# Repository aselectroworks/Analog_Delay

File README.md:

Analog_Delay
============

Multiple function BBD Analog Delay assisted by Digital Domain. 

### Features
* Max. 1000 ms delay by 4 BBDs
* Stereo In/Out
* Monaural In/Stereo Out(ping-pong or fx+dryout)
* Tap tempo function assisted by digital domain 
* Delay effect remain or bypass selectable when fx function off
* LCD display

### Design Tools
* [KiCAD](http://www.kicad-pcb.org/)
* [atmel studio 6](http://www.atmel.com/tools/ATMELSTUDIO.aspx)

### Download
You can download this project in either [zip](https://github.com/aselectroworks/Analog_Delay/zipball/master) or [tar](https://github.com/aselectroworks/Analog_Delay/tarball/master) formats. 
You can also clone this project with [git](http://git-scm.com/) by runninng: 
```
$ git clone git://github.com/aselectroworks/Analog_Delay
```

### License
GPL v3

### Contact
atsushi.sasaki@aselectroworks.com

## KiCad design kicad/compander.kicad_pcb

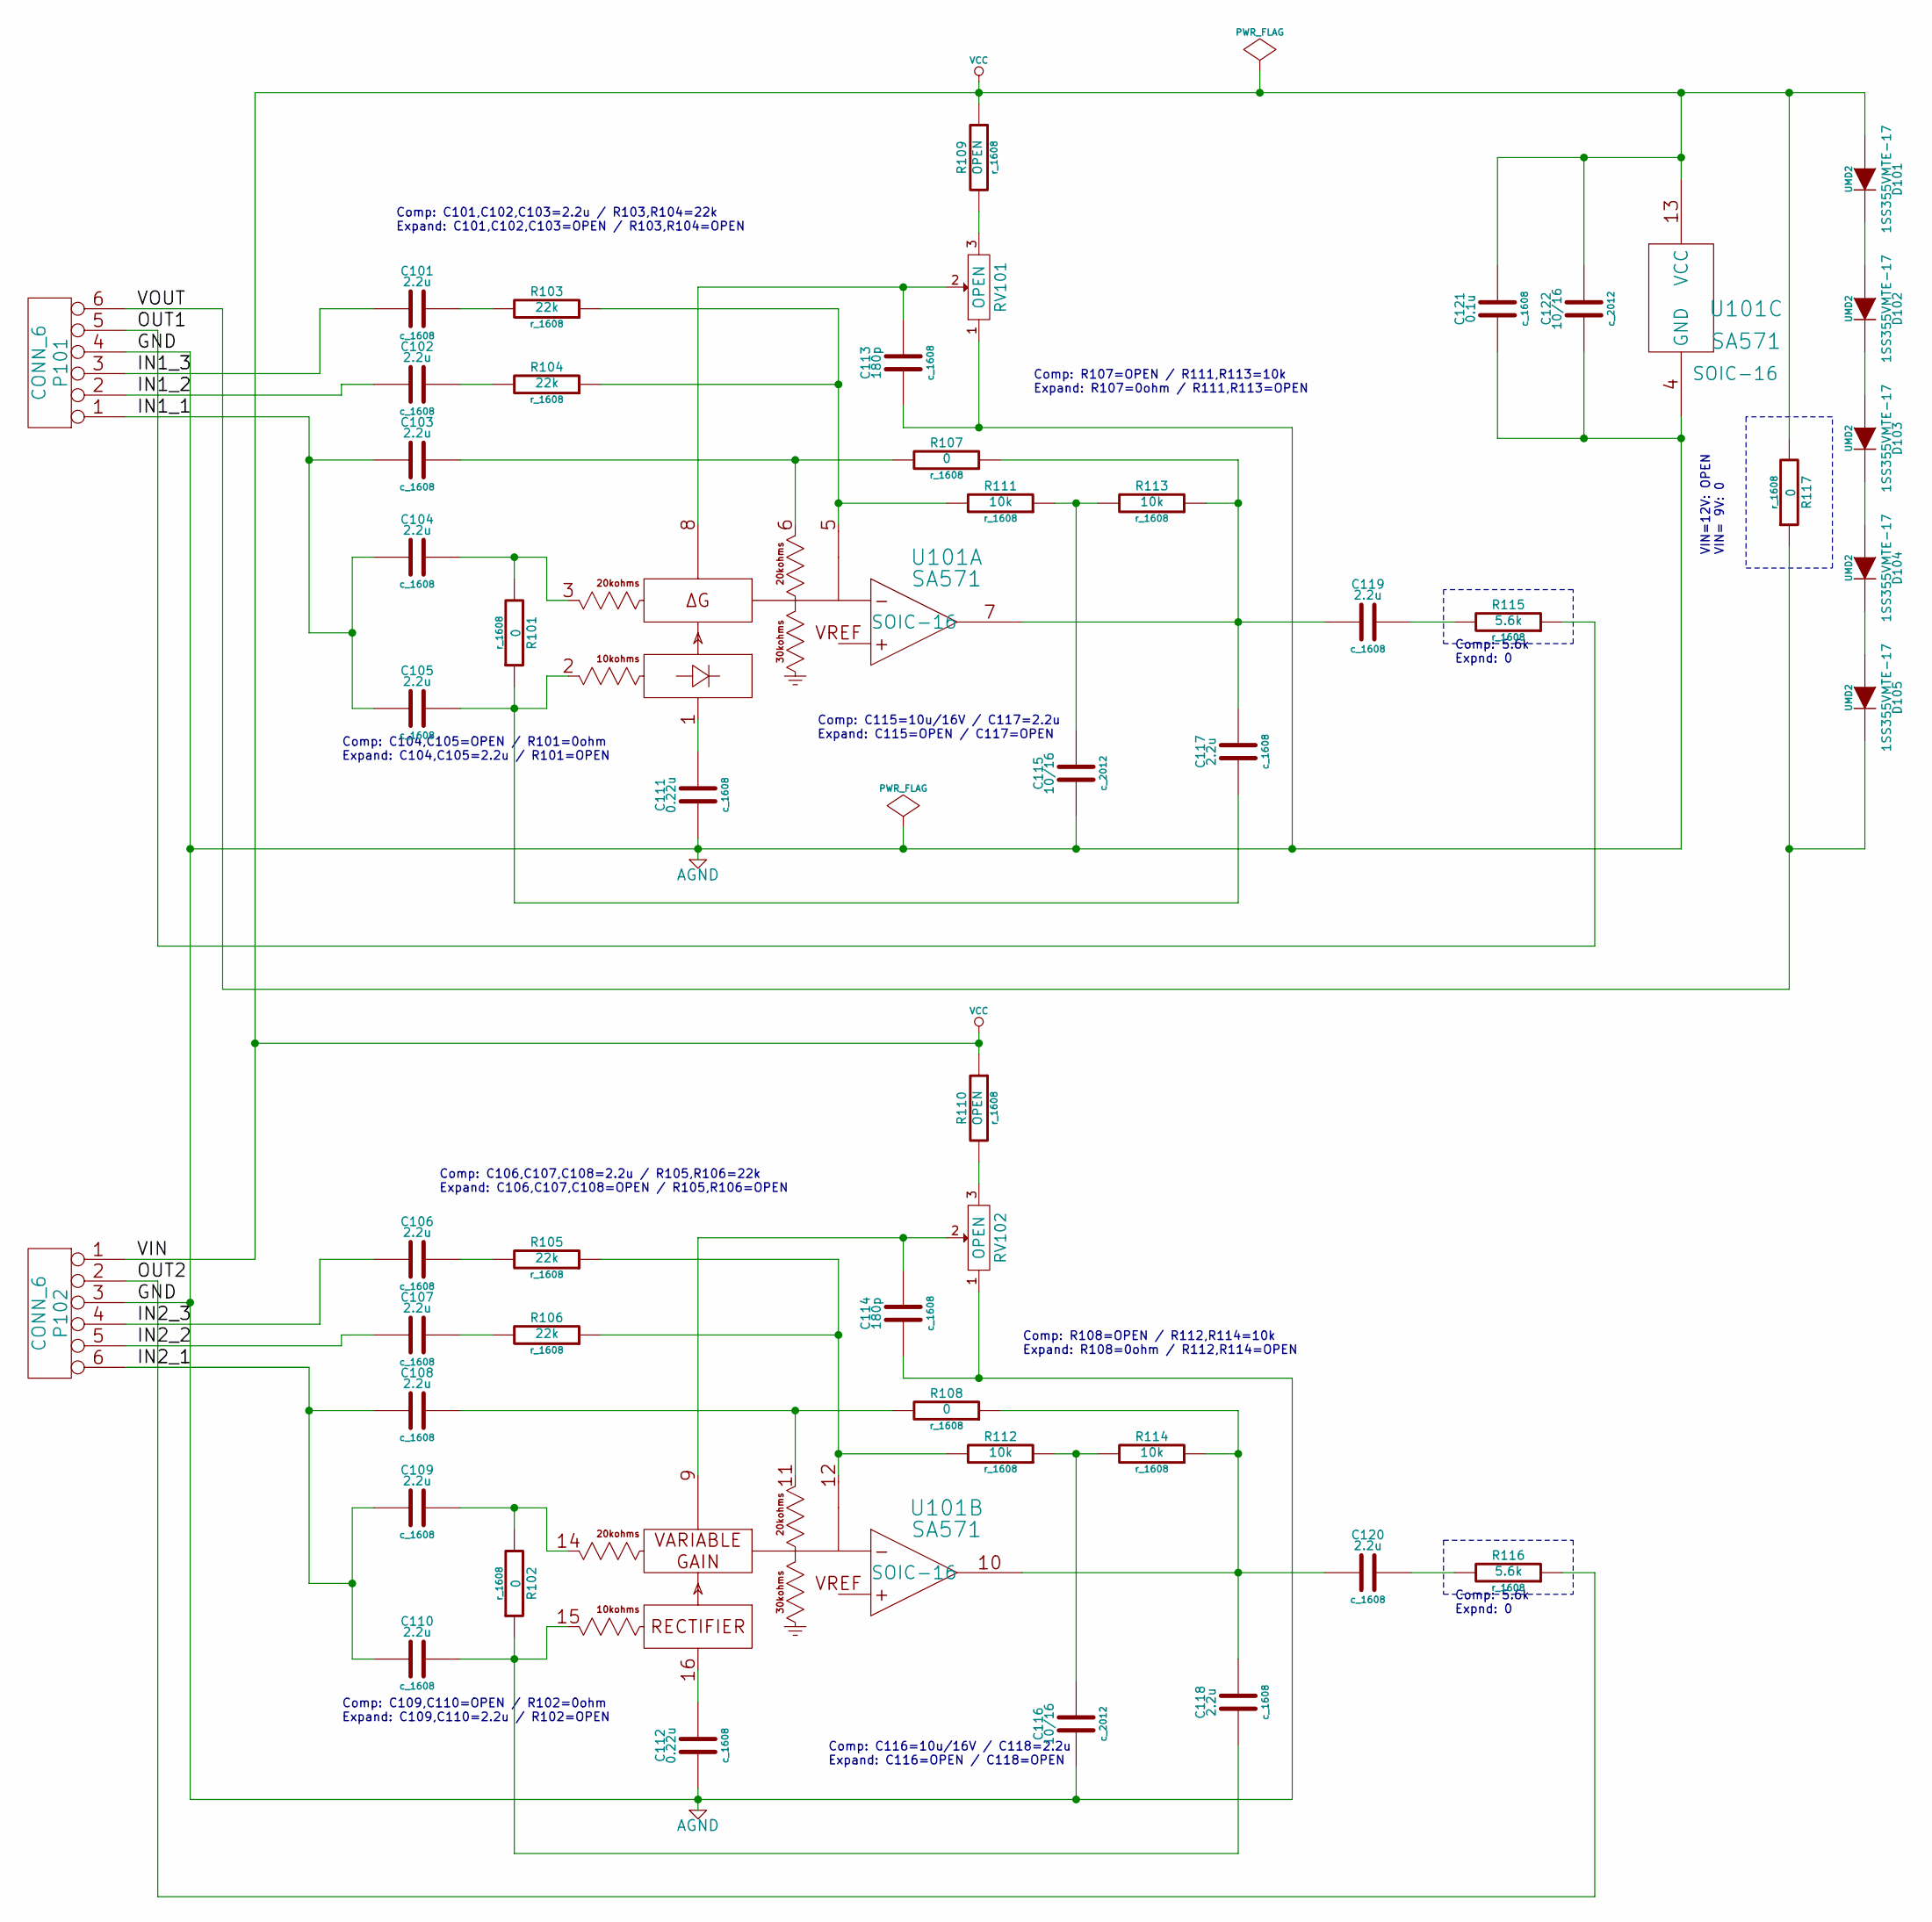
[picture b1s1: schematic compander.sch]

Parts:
C101, C102, C103, C104, C105, C106, C107, C108, C109, C110, C117, C118, C119, C120: 2.2u; c_1608
C111, C112: 0.22u; c_1608
C113, C114: 180p; c_1608
C115, C116, C122: 10/16; c_2012
C121: 0.1u; c_1608
D101, D102, D103, D104, D105: 1SS355VMTE-17; UMD2
P101, P102: CONN_6
R101, R102, R107, R108, R117: 0; r_1608
R103, R104, R105, R106: 22k; r_1608
R109, R110: OPEN; r_1608
R111, R112, R113, R114: 10k; r_1608
R115, R116: 5.6k; r_1608
RV101, RV102: OPEN
U101: SA571; SOIC-16

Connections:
/IN1_1: C103.1, C104.1, C105.1, P101.1
/IN1_2: C102.1, P101.2
/IN1_3: C101.1, P101.3
/IN2_1: C108.1, C109.1, C110.1, P102.6
/IN2_2: C107.1, P102.5
/IN2_3: C106.1, P102.4
/OUT1: P101.5, R115.1
/OUT2: P102.2, R116.1
/VOUT: D105.2 (K), P101.6, R117.1
AGND: C111.1, C112.1, C113.1, C114.1, C115.1, C116.1, C121.1, C122.1, P101.4, P102.3, RV101.1, RV102.1, U101.4 (GND)
unnamed: C114.2, RV102.2, U101.9 (THD_TRIM_2)
unnamed: R110.2, RV102.3
unnamed: C104.2, R101.2, U101.3 (DG_CELL_IN_1)
unnamed: R105.1, R106.1, R112.2, U101.12 (INV._IN_2)
unnamed: C107.2, R106.2
unnamed: C106.2, R105.2
unnamed: C120.2, R116.2
unnamed: C115.2, R111.1, R113.2
unnamed: R103.1, R104.1, R111.2, U101.5 (INV._IN_1)
unnamed: C102.2, R104.2
unnamed: C101.2, R103.2
unnamed: C119.2, R115.2
unnamed: C105.2, C117.1, R101.1, U101.2 (RECT_IN_1)
unnamed: C116.2, R112.1, R114.2
unnamed: C111.2, U101.1 (RECT_CAP_1)
unnamed: C103.2, R107.2, U101.6 (RES._R3_1)
unnamed: C117.2, C119.1, R107.1, R113.1, U101.7 (OUTPUT_1)
unnamed: D101.2 (K), D102.1 (A)
unnamed: D104.2 (K), D105.1 (A)
unnamed: D103.2 (K), D104.1 (A)
unnamed: D102.2 (K), D103.1 (A)
unnamed: C112.2, U101.16 (RECT_CAP_2)
unnamed: C108.2, R108.2, U101.11 (RES._R3_2)
unnamed: C118.2, C120.1, R108.1, R114.1, U101.10 (OUTPUT_2)
unnamed: C110.2, C118.1, R102.1, U101.15 (RECT_IN_2)
unnamed: C109.2, R102.2, U101.14 (DG_CELL_IN_2)
unnamed: C113.2, RV101.2, U101.8 (THD_TRIM_1)
unnamed: R109.2, RV101.3
VCC: C121.2, C122.2, D101.1 (A), P102.1, R109.1, R110.1, R117.2, U101.13 (VCC)

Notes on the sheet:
Comp: 5.6k Expnd: 0
VIN=12V: OPEN VIN= 9V: 0
Comp: C104,C105=OPEN / R101=0ohm Expand: C104,C105=2.2u / R101=OPEN
Comp: C109,C110=OPEN / R102=0ohm Expand: C109,C110=2.2u / R102=OPEN
Comp: C106,C107,C108=2.2u / R105,R106=22k Expand: C106,C107,C108=OPEN / R105,R106=OPEN
Comp: C101,C102,C103=2.2u / R103,R104=22k Expand: C101,C102,C103=OPEN / R103,R104=OPEN
Comp: R107=OPEN / R111,R113=10k Expand: R107=0ohm / R111,R113=OPEN
Comp: R108=OPEN / R112,R114=10k Expand: R108=0ohm / R112,R114=OPEN
Comp: C116=10u/16V / C118=2.2u Expand: C116=OPEN / C118=OPEN
Comp: C115=10u/16V / C117=2.2u Expand: C115=OPEN / C117=OPEN

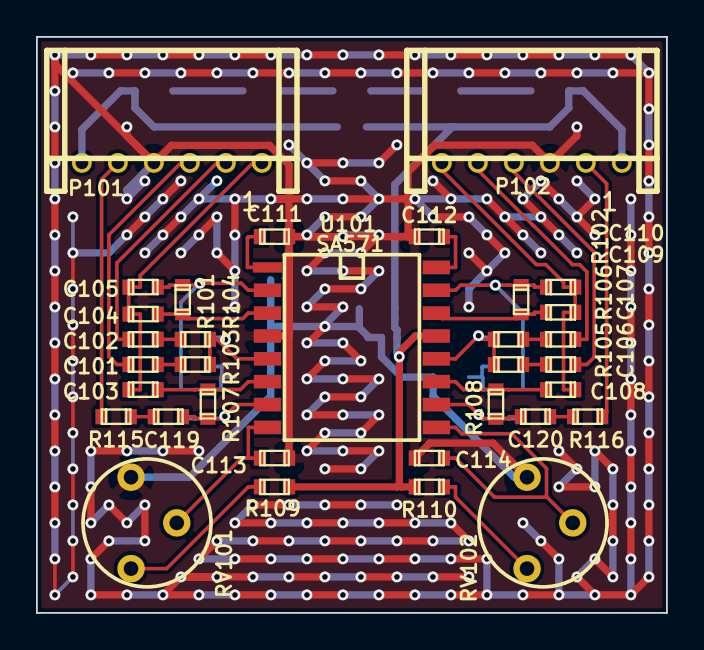
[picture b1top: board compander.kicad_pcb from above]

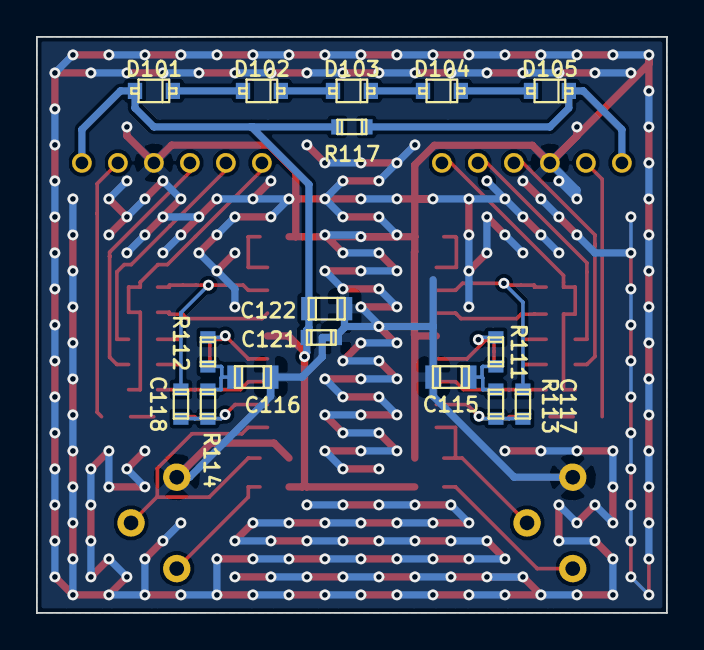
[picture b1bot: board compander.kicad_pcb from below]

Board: 2 copper layers, 35.0 x 32.0 mm, 49 parts (16 on the bottom side), 39 nets.

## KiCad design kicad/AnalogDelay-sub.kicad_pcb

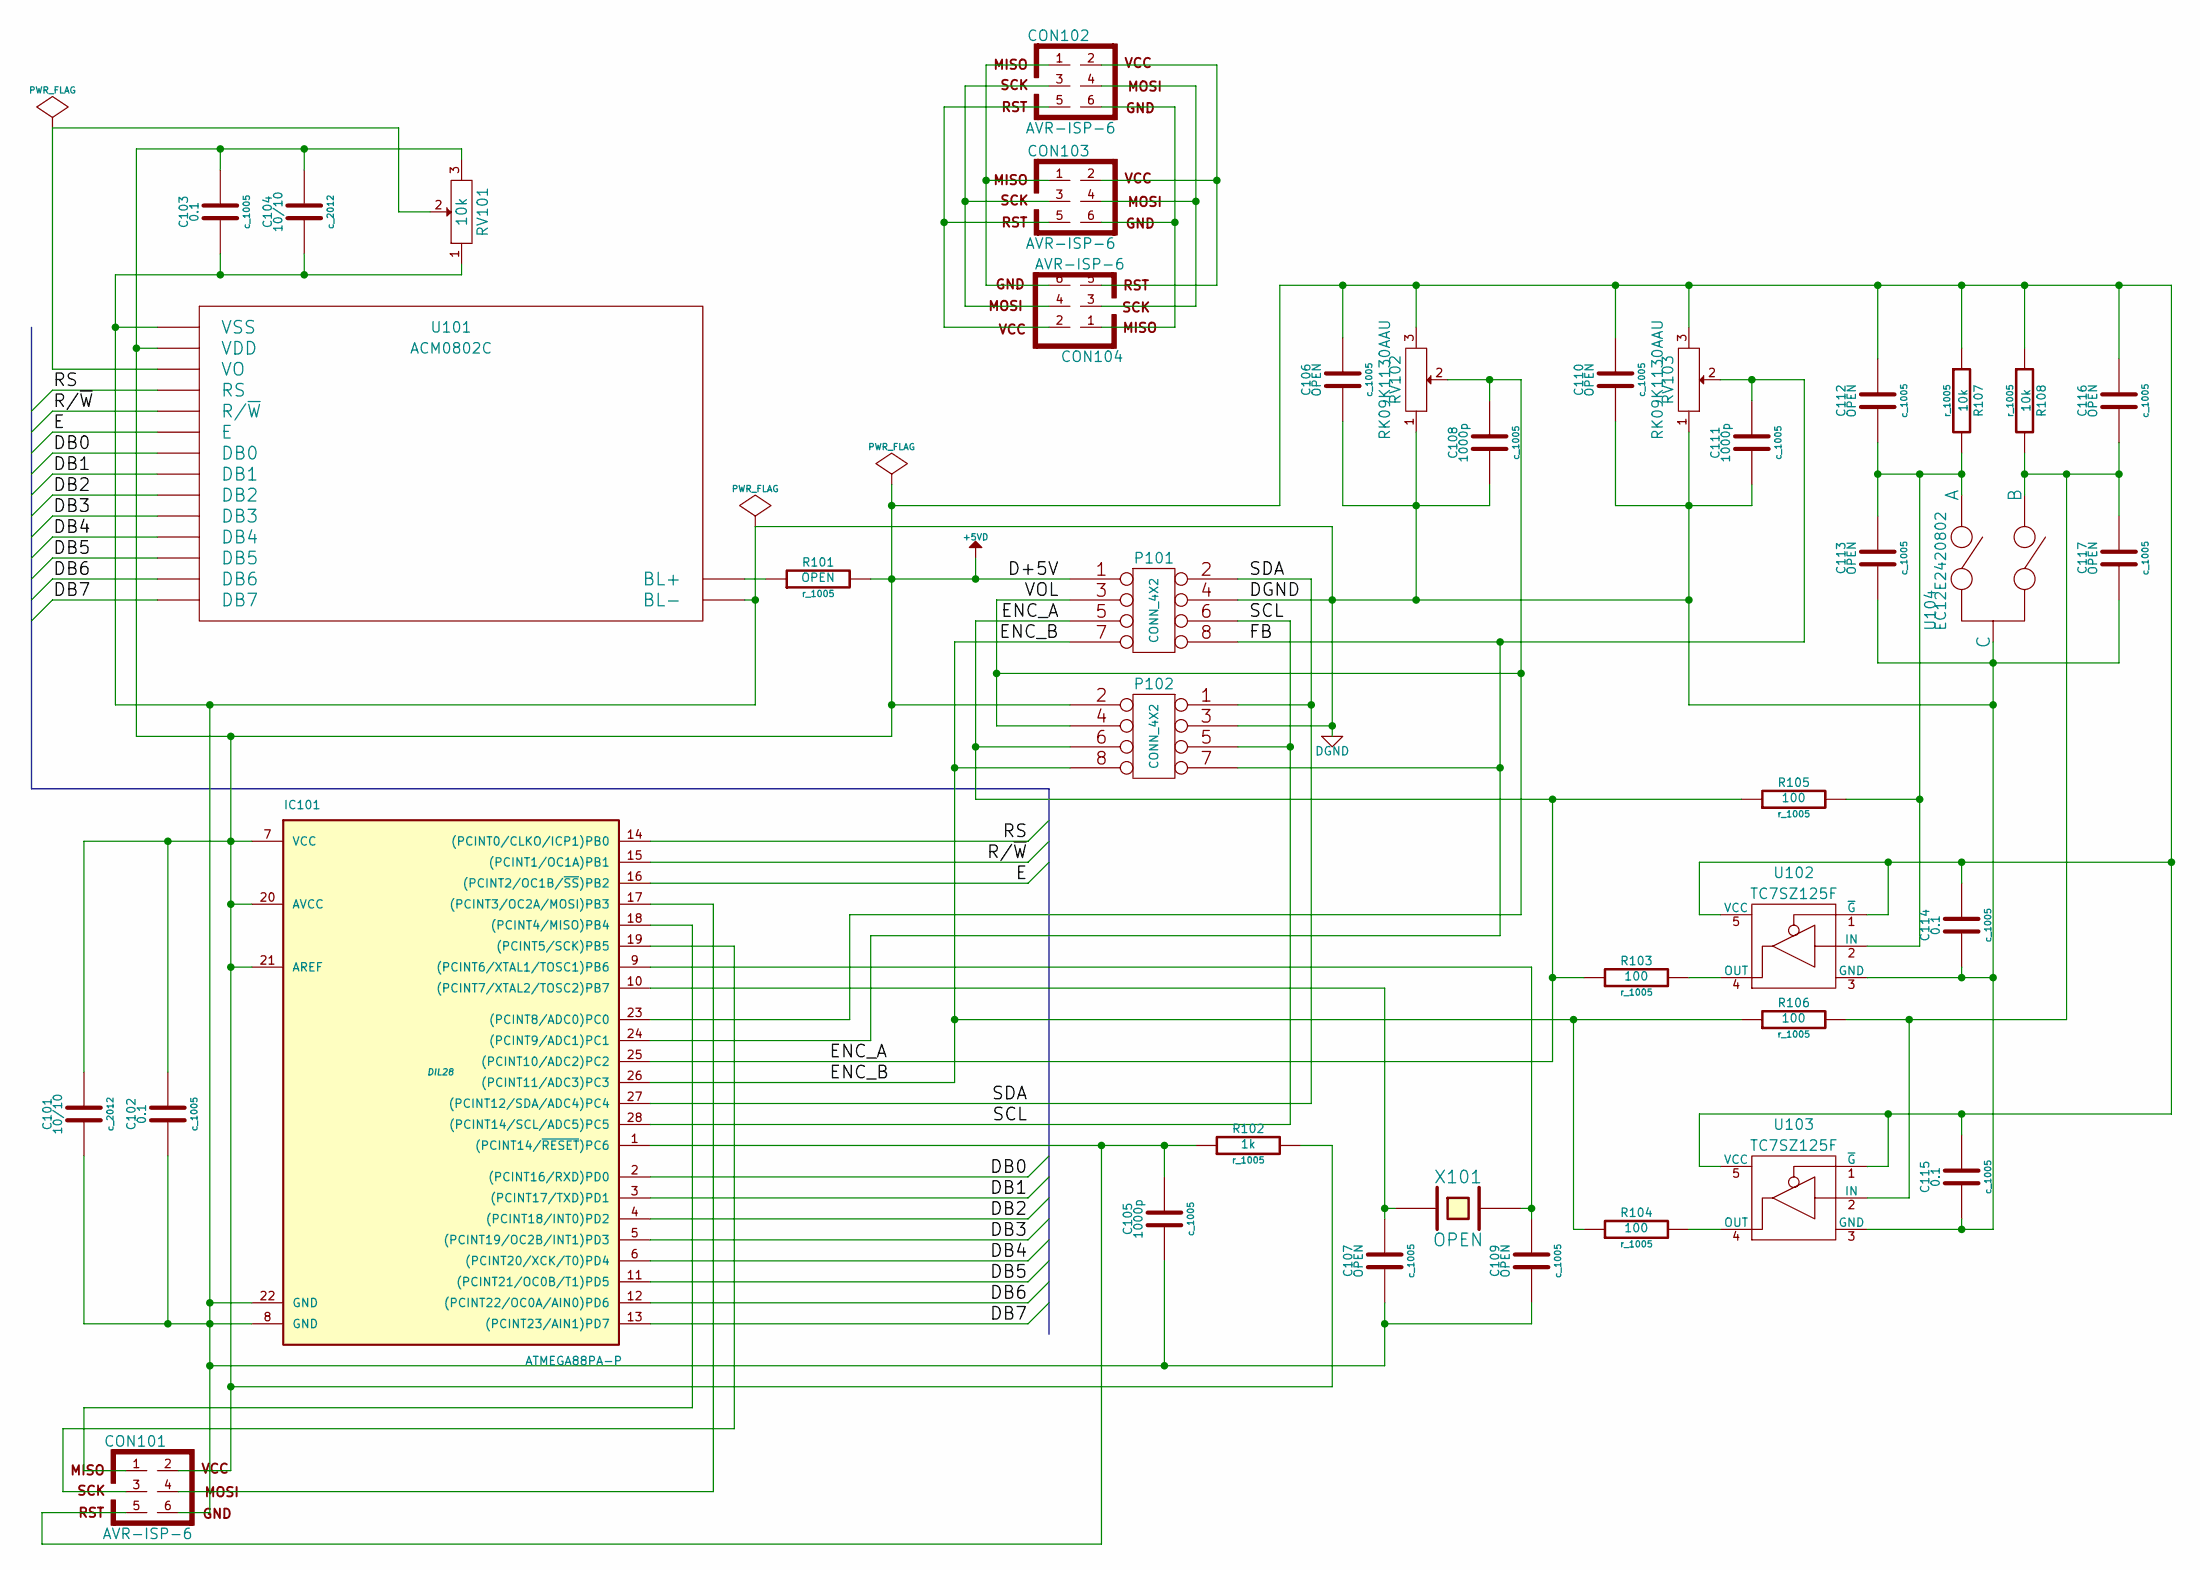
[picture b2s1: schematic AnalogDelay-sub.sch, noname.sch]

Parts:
C101, C104: 10/10; c_2012
C102, C103, C114, C115: 0.1; c_1005
C105, C108, C111: 1000p; c_1005
C106, C107, C109, C110, C112, C113, C116, C117: OPEN; c_1005
CON101, CON102, CON103, CON104: AVR-ISP-6
IC101: ATMEGA88PA-P; DIL28
P101, P102: CONN_4X2
R101: OPEN; r_1005
R102: 1k; r_1005
R103, R104, R105, R106: 100; r_1005
R107, R108: 10k; r_1005
RV101: 10k
RV102, RV103: RK09K1130AAU
U101: ACM0802C
U102, U103: TC7SZ125F; SC74-A
U104: EC12E2420802; EC12E-BUSHING-20
X101: OPEN

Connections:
+5VD: C101.2, C102.2, C103.2, C104.2, C106.2, C110.2, C112.2, C114.2, C115.2, C116.2, CON101.2, IC101.7 (VCC), IC101.20 (AVCC), IC101.21 (AREF), P101.1, P102.2, R101.2, R102.2, R107.1, R108.1, RV101.3, RV102.3, RV103.3, U101.2 (VDD), U102.1 (~G), U102.5 (VCC), U103.1 (~G), U103.5 (VCC)
/DB0: IC101.2 ((PCINT16/RXD)PD0), U101.7 (DB0)
/DB1: IC101.3 ((PCINT17/TXD)PD1), U101.8 (DB1)
/DB2: IC101.4 ((PCINT18/INT0)PD2), U101.9 (DB2)
/DB3: IC101.5 ((PCINT19/OC2B/INT1)PD3), U101.10 (DB3)
/DB4: IC101.6 ((PCINT20/XCK/T0)PD4), U101.11 (DB4)
/DB5: IC101.11 ((PCINT21/OC0B/T1)PD5), U101.12 (DB5)
/DB6: IC101.12 ((PCINT22/OC0A/AIN0)PD6), U101.13 (DB6)
/DB7: IC101.13 ((PCINT23/AIN1)PD7), U101.14 (DB7)
/E: IC101.16 ((PCINT2/OC1B/~SS~)PB2), U101.6 (E)
/ENC_A: IC101.25 ((PCINT10/ADC2)PC2), P101.5, P102.6, R103.1, R105.1
/ENC_B: IC101.26 ((PCINT11/ADC3)PC3), P101.7, P102.8, R104.1, R106.1
/FB: C111.2, IC101.24 ((PCINT9/ADC1)PC1), P101.8, P102.7, RV103.2
/R/~W: IC101.15 ((PCINT1/OC1A)PB1), U101.5 (R/~W)
/RS: IC101.14 ((PCINT0/CLKO/ICP1)PB0), U101.4 (RS)
/SCL: IC101.28 ((PCINT14/SCL/ADC5)PC5), P101.6, P102.5
/SDA: IC101.27 ((PCINT12/SDA/ADC4)PC4), P101.2, P102.1
/VOL: C108.2, IC101.23 ((PCINT8/ADC0)PC0), P101.3, P102.4, RV102.2
DGND: C101.1, C102.1, C103.1, C104.1, C105.1, C106.1, C107.1, C108.1, C109.1, C110.1, C111.1, C113.1, C114.1, C115.1, C117.1, CON101.6, IC101.8 (GND), IC101.22 (GND), P101.4, P102.3, RV101.1, RV102.1, RV103.1, U101.1 (VSS), U101.16 (BL-), U102.3 (GND), U103.3 (GND), U104.3 (C)
unnamed: CON101.1, IC101.18 ((PCINT4/MISO)PB4)
unnamed: CON101.4, IC101.17 ((PCINT3/OC2A/MOSI)PB3)
unnamed: CON101.3, IC101.19 ((PCINT5/SCK)PB5)
unnamed: C109.2, IC101.9 ((PCINT6/XTAL1/TOSC1)PB6), X101.2
unnamed: C107.2, IC101.10 ((PCINT7/XTAL2/TOSC2)PB7), X101.1
unnamed: CON102.3, CON103.3, CON104.4
unnamed: CON102.2, CON103.2, CON104.5
unnamed: CON102.1, CON103.1, CON104.6
unnamed: CON102.5, CON103.5, CON104.2
unnamed: CON102.6, CON103.6, CON104.1
unnamed: CON102.4, CON103.4, CON104.3
unnamed: C105.2, CON101.5, IC101.1 ((PCINT14/~RESET~)PC6), R102.1
unnamed: RV101.2, U101.3 (VO)
unnamed: R101.1, U101.15 (BL+)
unnamed: R104.2, U103.4 (OUT)
unnamed: R103.2, U102.4 (OUT)
unnamed: C112.1, C113.2, R105.2, R107.2, U102.2 (IN), U104.1 (A)
unnamed: C116.1, C117.2, R106.2, R108.2, U103.2 (IN), U104.2 (B)

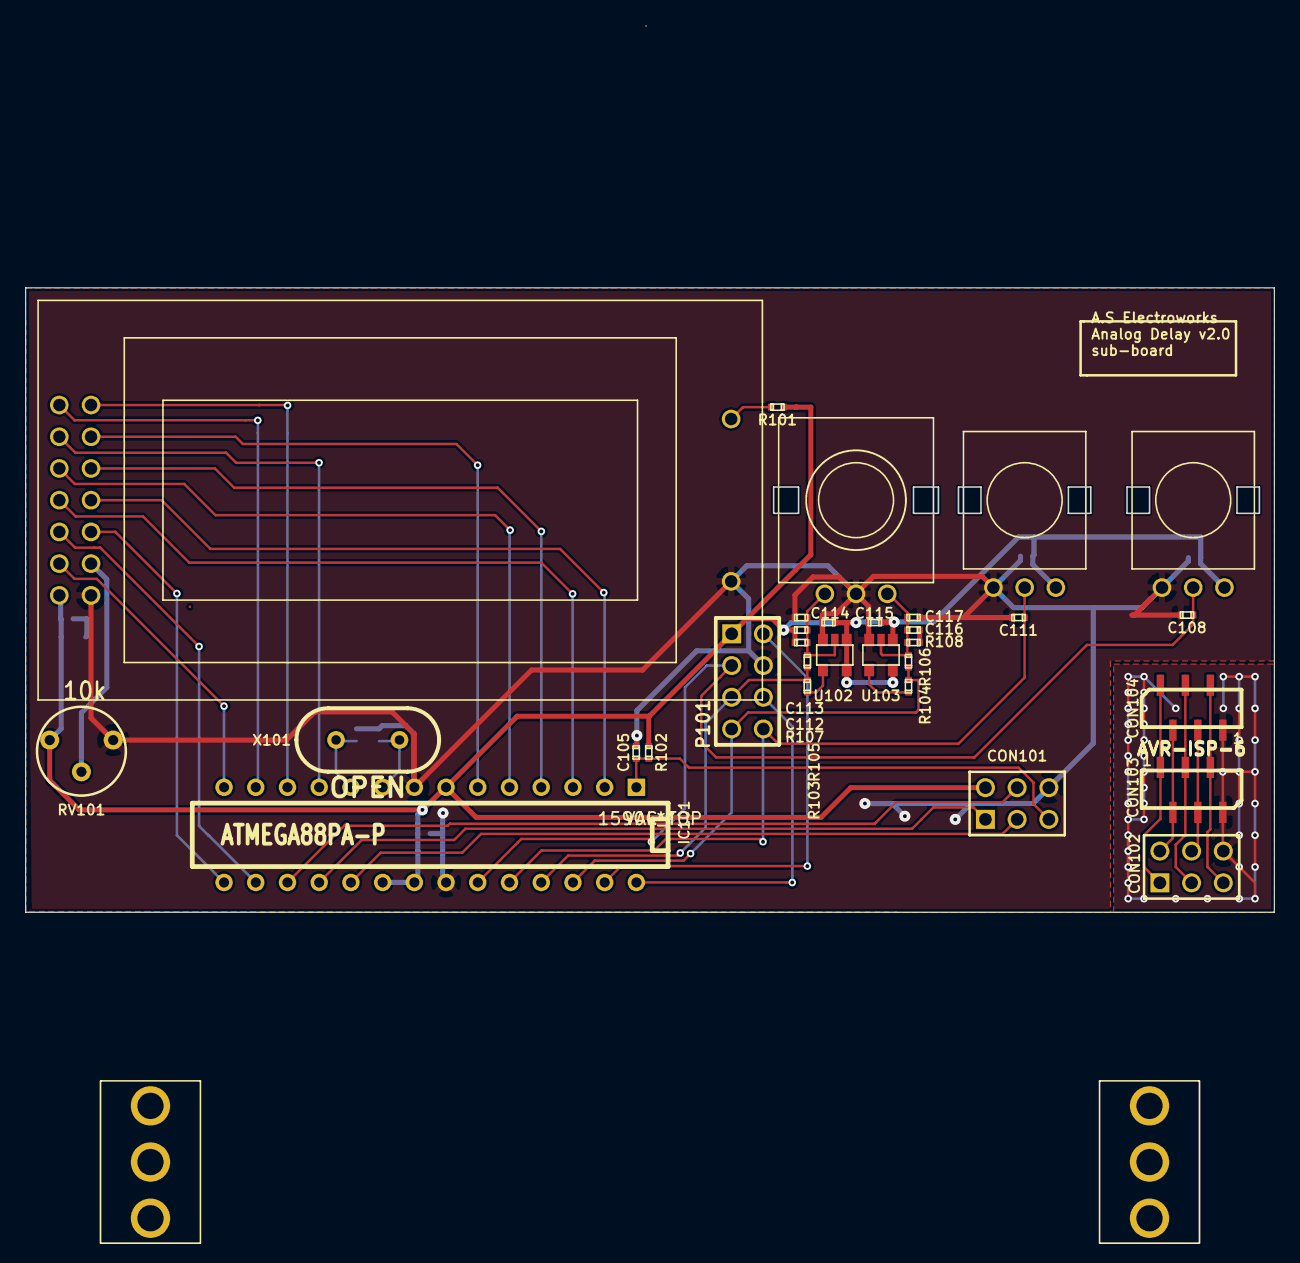
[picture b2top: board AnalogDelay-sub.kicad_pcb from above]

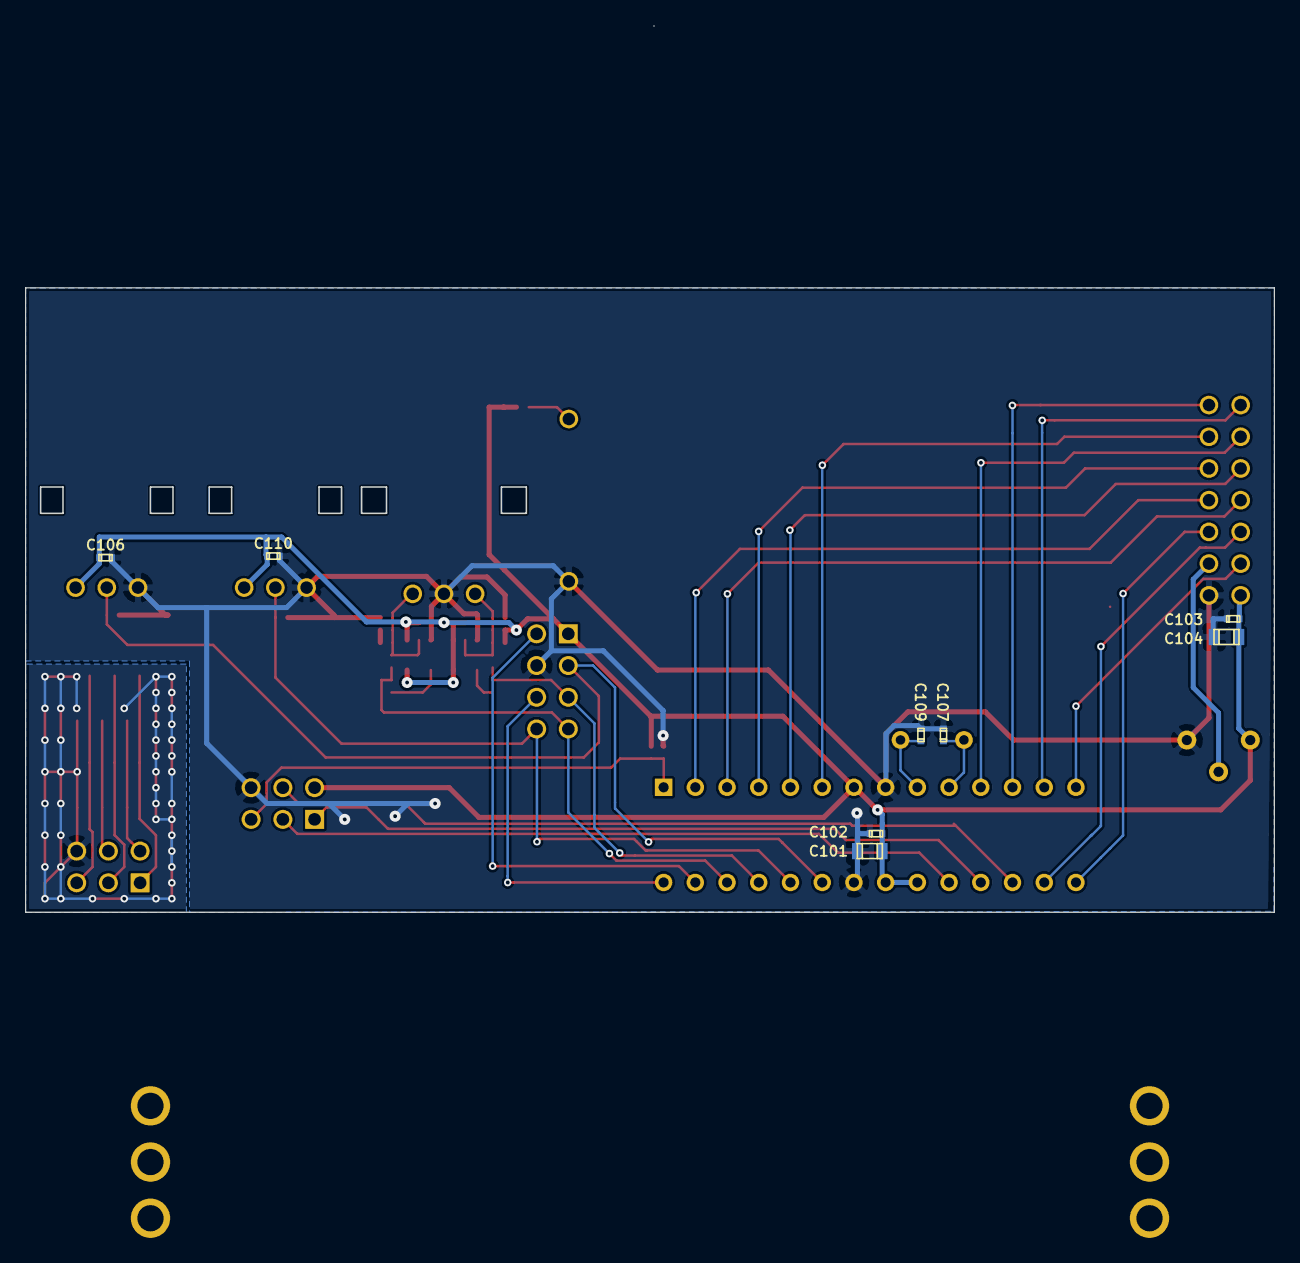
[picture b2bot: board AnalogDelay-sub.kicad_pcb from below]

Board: 2 copper layers, 100.0 x 50.0 mm, 43 parts (8 on the bottom side), 37 nets.

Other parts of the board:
1590C_SIDE: VAL**; 1590C_SIDE
1590C_TOP: VAL**; 1590C_TOP
SW***: 8Y10XX; 8Y10
SW***#2: 8Y10XX; 8Y10
